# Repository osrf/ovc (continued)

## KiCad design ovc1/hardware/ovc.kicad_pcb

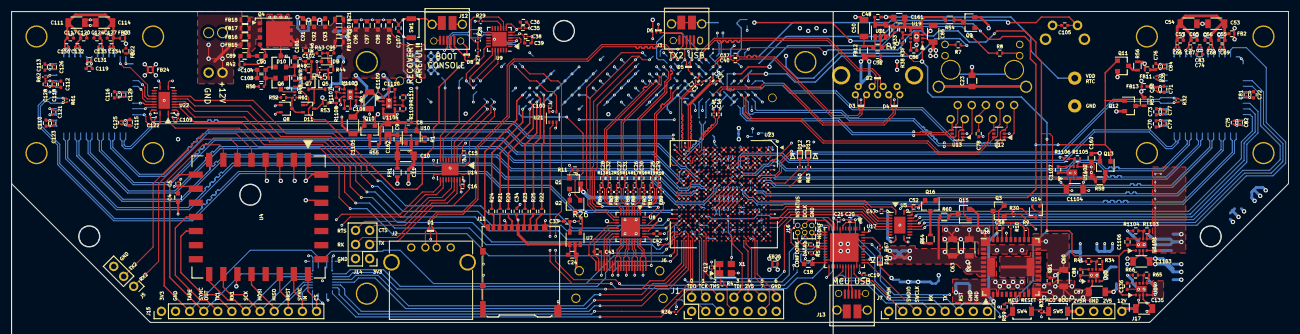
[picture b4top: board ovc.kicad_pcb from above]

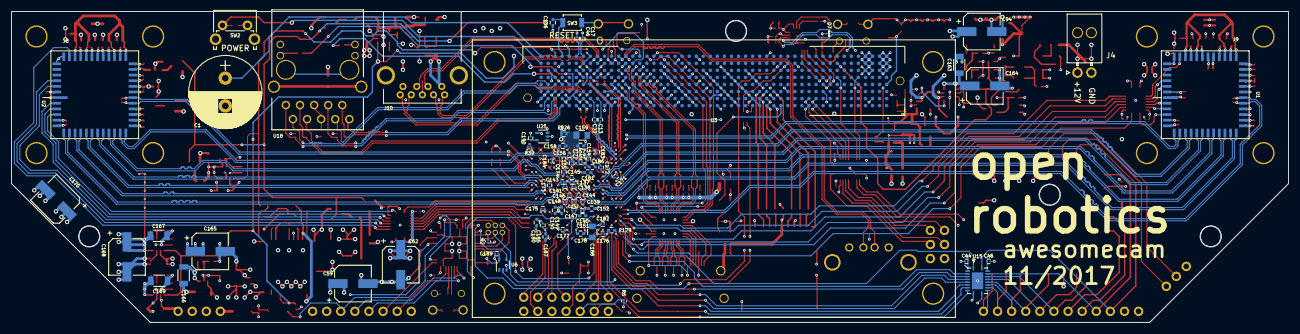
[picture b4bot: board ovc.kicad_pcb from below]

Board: 6 copper layers, 230.0 x 56.0 mm, 379 parts (80 on the bottom side), 315 nets.

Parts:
C1: 100m; CP_Radial_D13.0mm_P5.00mm
C2, C3, C5, C6, C7, C13, C14, C15, C16, C17, C19, C20, C21, C22, C25, C26, C27, C28, C29, C30, C31, C32, C35, C37, C38, C40, C41, C44, C45, C46, C47, C52, C77, C79, C80, C81, C82, C83, C84, C100, C109, C121, C122, C123, C125, C126, C128, C129, C131, C146, C147, C154, C155, C175, C176, C183, C184, C189, C190: 100n; C_0201
C4, C9, C18, C24, C49, C91, C92, C93, C96, C97, C98, C99, C103, C104: 10u; C_0603
C8, C11, C34, C42, C48, C51, C61: 100n; C_0402
C10, C50, C53, C54, C63, C64, C111, C114, C163, C166, C167, C169: 100u; C_1206
C12, C75, C118, C143, C171: 10n; C_0201
C23: 100p; C_0805
C33, C43, C102, C150, C158, C179, C187: 1u; C_0402
C36, C39, C55, C56, C57, C65, C74, C76, C116, C117, C119, C120, C124, C127, C151, C152, C180, C181: 4u7; C_0402
C58, C78: 10n; C_0402
C59, C94: 100u; CP_Elec_6.3x7.7
C60, C85, C87, C135, C1103, C1104, C1105, C1109: 47u; C_1206
C62, C164, C165, C168, C170: 220u; CP_Elec_6.3x5.8
C66, C67, C68, C69, C130, C132, C133, C134: 1u; C_0201
C70, C71, C72, C73, C110, C112, C113, C115: 10u; C_0402
C86, C88, C108, C136, C1106, C1107, C1110: 4n7; C_0402
C89: 100n; C_0603
C90: 4u7; C_0603
C95, C149, C157, C178, C186: 470n; C_0402
C101: 2u2; C_0603
C105, C106, C107: 1n; C_0402
C137, C138, C139, C140, C141, C142, C153, C172, C182: 22n; C_0201
C144, C145, C173, C174: 47n; C_0201
C148, C156, C177, C185: 220n; C_0201
C159, C188: 100u; C_0805
C160: 22u; C_0603
C161, C162: 22u; C_0805
D1, D2, D3, D4, D5, D6, D7, D8: TPD2EUSB30A; TPD2EUSB30x
D9: RB521S30T1G; D_SOD-523
D10: BAT54ALT1G; SOT-23
D11: BAT54CW-7-F; SOT-323_SC-70
D12, D14: LED_Red; LED_0402
D13: LED_Green; LED_0402
FB1, FB12: 220; R_0603
FB2, FB11, FB13, FB22, FB23, FB24: 220; R_0402
FB3, FB4, FB5, FB6, FB7, FB8, FB9, FB10: 600; R_0201
FB15, FB16, FB17, FB18, FB19, FB20, FB21: 30; R_0603
FB25, FB26: 60; R_0402
J1: FPGA DEBUG; Pin_Header_Straight_2x07_Pitch2.54mm
J2: USB_A
J3, J12, J13: USB_OTG; USB_Micro-B_10103594-0001LF
J4: POWER; Molex_NanoFit_1x02x2.50mm_Angled
J5: IMU DEBUG; Pin_Header_Straight_1x03_Pitch2.54mm
J6: HDMI_TYPE_A; AMP_FCI_10029449-111RLF_HDMI_TYPE_A
J7: MCU DEBUG; Pin_Header_Straight_1x08_Pitch2.54mm
J8, J9: LENS_HOLDER; M12_PYTHON1300_M3Mounting
J10: USB3_A; wurth_692121030100
J11: Micro_SD_Card_Det_Hirose_DM3AT; Hirose_DM3AT-SF-PEJM5
J14: DEBUG UART; Pin_Header_Straight_2x03_Pitch2.54mm
J15: IMU; Pin_Header_Straight_1x12_Pitch2.54mm
J16: FPGA CONFIG; Pin_Header_Straight_2x03_Pitch1.27mm
J17: POWER DEBUG; Pin_Header_Straight_1x04_Pitch2.54mm
Q1: Q_NMOS_GSD; SOT-23
Q2, Q3: DMN2041L; SOT-23
Q4: AON6407; TDSON-8-1
Q5, Q7, Q8, Q14: NTS4001NT1G; SOT-323_SC-70
Q6: MMBT4403; SOT-23
Q9, Q10, Q11, Q12, Q13, Q15, Q16: NTR4003NT1G; SOT-23
R1, R11, R33, R42, R44, R46, R47, R48: 10k; R_0402
R2, R3, R4, R5, R6, R27, R28, R30, R31: 10k; R_0201
R7, R8: 681; R_0402
R9: 1M; R_0201
R10: 1k74; R_0201
R12, R13, R14, R15, R16, R17, R18, R19: 499; R_0201
R20: 0; R_0402
R21, R22, R23, R24, R25: 10; R_0402
R26, R35, R45, R51, R62: 47k; R_0201
R29, R36: 1k; R_0201
R32, R61: 100; R_0201
R34, R65: 215k; R_0402
R37, R1109: 523k; R_0402
R38, R41, R43, R49, R52, R53, R59, R66, R1104, R1106, R1108, R1110: 100k; R_0402
R39: 2k; R_0201
R40, R63, R67: 330; R_0201
R50: 10M; R_0402
R54, R55: 100; R_0603
R56, R57, R58, R60, R64: 47; R_0603
R1103: 316k; R_0402
R1105: 49k9; R_0402
R1107: 124k; R_0402
SW1: recovery; SW_SPST_B3U-1000P
SW2: SW_Push; SW_Tactile_SPST_Angled_PTS645Vx58-2LFS
SW3: SW_Push; SW_SPST_B3U-1000P
SW4: RESET; SW_SPST_B3U-1000P
SW5: BOOT; SW_SPST_B3U-1000P
U1, U2: NOIP1SN1300A-QDI; LCC101.6P1422X1422X165-48
U3: Jetson; JETSON_TX
U4: VN-100
U5, U14, U15, U22: TXB0108RGY; TI_VQFN_20_RGY
U6, U21, U25: 74LVC1G34; SOT-353_SC-70-5
U7: NCP380LSN10AAT1G; SOT-23-5
U8: IP4786CZ32; QFN-32-1EP_5x5mm_Pitch0.5mm
U9: CP2102N-A01-GQFN24; QFN-24-1EP_4x4mm_Pitch0.5mm
U10, U11: TPS2069C; SOT-23-5
U12, U13: SP3002-04JTG; SOT-363_SC-70-6
U16: LMZ31707; TI_RVQ_42
U17: STM32L452CE; QFN-48-1EP_7x7mm_Pitch0.5mm
U18: ARJ11C-MBSAS-A-BA-7MU2
U19, U20, U24, U1101, U1102, U1103, U1104: TPS82130
U23: 5CGTFD5C5U19I7N; INTEL_U484
X1: ASEMB-100MHz; Oscillator_SMD_Abracon_ASE-4pin_3.2x2.5mm

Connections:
2V5_MCU: C18.1, C19.1, C21.1, C165.1, C166.1, C189.1, J7.1, J17.4, R30.1, R34.1, R59.2, SW5.1, U6.5, U17.1, U17.9, U17.24, U17.36, U17.48, U20.4, U20.5
+1V1: C62.1, C63.1, C64.1, C137.1, C138.1, C139.1, C140.1, C141.1, C142.1, C143.1, C144.1, C145.1, C146.1, C147.1, C148.1, C149.1, C150.1, C151.1, C152.1, R60.1, U16.27, U16.34, U16.35, U16.36, U16.37, U16.38, U16.41, U23.H11, U23.H13, U23.H15, U23.J10, U23.J12, U23.J14, U23.K9, U23.K11, U23.K13, U23.L10, U23.L12, U23.L14, U23.M11, U23.M13, U23.M15, U23.N12, U23.N14, U23.P11, U23.P13, U23.P15
+1V2: C160.1, FB26.2, R58.1, R1105.1, U1102.4, U1102.5
+1V8: C15.1, C38.1, C39.1, C100.1, C163.1, C164.1, FB13.2, FB24.2, R29.2, R57.1, R1107.1, U8.27, U8.28, U9.5, U14.2, U14.10, U17.38, U21.5, U1103.4, U1103.5
+2V5: C12.1, C44.1, C47.1, C109.1, C169.1, C170.1, C171.1, C172.1, C173.1, C174.1, C175.1, C176.1, C177.1, C178.1, C179.1, C180.1, C181.1, C190.1, FB25.2, J1.9, J17.2, R2.1, R3.1, R4.1, R5.1, R6.1, R64.1, R65.1, U5.2, U5.10, U15.2, U15.10, U22.2, U22.10, U23.A6, U23.A16, U23.AA6, U23.AA21, U23.AB9, U23.AB14, U23.B7, U23.B9, U23.B19, U23.C5, U23.C12, U23.D15, U23.E8, U23.E9, U23.E15, U23.E18, U23.F9, U23.F13, U23.G19, U23.H7, U23.H17, U23.H22, U23.K18, U23.L21, U23.M18, U23.N17, U23.N19, U23.P17, U23.P20, U23.R8, U23.R18, U23.T6, U23.T16, U23.T21, U23.U20, U23.V6, U23.V7, U23.V10, U23.V12, U23.V14, U23.V16, U23.W9, U23.W10, U23.W15, U23.Y6, U23.Y18, U24.4, U24.5, U25.5, X1.1, X1.4
+3V3: C4.1, C5.1, C16.1, C33.1, C35.1, C36.1, C45.1, C52.1, C122.1, C167.1, C168.1, FB2.2, FB11.2, FB22.2, FB23.2, J14.1, J15.1, R11.1, R26.1, R56.1, R1103.1, U4.10, U5.19, U7.5, U9.6, U9.7, U14.19, U15.19, U18.12, U18.13, U22.19, U1101.4, U1101.5
+5V: C8.1, C162.1, R55.1, R1109.1, U8.11, U10.5, U1104.4, U1104.5
+12V: C59.1, C60.1, C61.1, C85.1, C87.1, C91.1, C92.1, C93.1, C95.1, C135.1, C1103.1, C1104.1, C1105.1, C1109.1, D10.3, FB19.2, FB20.2, FB21.2, J17.1, Q4.5, R46.1, R51.1, U16.1, U16.3, U16.11, U16.12, U16.39, U16.40, U19.2, U20.2, U24.2, U1101.2, U1102.2, U1103.2, U1104.2
/IMU/CS_3V3: J15.12, U4.23, U15.12
/IMU/MISO_3V3: J15.9, U4.19, U15.15
/IMU/MOSI_3V3: J15.8, U4.17, U15.16
/IMU/NRST_3V3: J15.10, U4.21, U15.14
/IMU/RX2: J5.1, U4.6
/IMU/SCK_3V3: J15.7, U4.16, U15.17
/IMU/SYNC_IN_3V3: J15.11, U4.22, U15.13
/IMU/SYNC_OUT_3V3: J15.4, U4.9, U15.18
/IMU/TARE_3V3: J15.3, U4.7, U15.20
/IMU/TX2: J5.2, U4.5
/fpga_bank_5b/CLK100: U23.L17, X1.3
/fpga_bank_8a/LED0: R40.2, U23.A9
/fpga_bank_8a/LED1: R63.2, U23.A10
/fpga_config/TCK: J1.3, R36.1, U23.V5
/fpga_config/TDI: J1.7, R4.2, U23.P5
/fpga_config/TDO: J1.1, U23.V3
/fpga_config/TMS: J1.5, R6.2, U23.R4
/fpga_pcie/GXB_TX_L0+: C22.2, U23.Y4
/fpga_pcie/GXB_TX_L0-: C13.2, U23.Y3
/fpga_pcie/GXB_TX_L1+: C14.2, U23.U2
/fpga_pcie/GXB_TX_L1-: C41.2, U23.U1
/fpga_pcie/REFCLK+: C17.2, U23.V4
/fpga_pcie/REFCLK-: C46.2, U23.U4
/fpga_power/RREF_TL: R39.1, U23.A1
/fpga_power/VCC_AUX: C182.1, C183.1, C184.1, C185.1, C186.1, C187.1, C188.1, FB25.1, U23.A3, U23.AA12, U23.AB5, U23.D6, U23.D12, U23.D19, U23.E19, U23.F4, U23.M3, U23.T3, U23.T4, U23.U18, U23.W19
/fpga_power/VCC_GXBL: C153.1, C154.1, C155.1, C156.1, C157.1, C158.1, C159.1, FB26.1, U23.J4, U23.K3, U23.K5, U23.L4, U23.N4, U23.P3
/imagers/CAM1_1V8: C112.1, C115.1, C118.1, C121.1, C125.1, C128.1, FB24.1, U1.6, U1.22, U1.26
/imagers/CAM1_3V3: C110.1, C113.1, C116.1, C119.1, C123.1, C126.1, C129.1, C131.1, FB22.1, U1.1, U1.19, U1.29, U1.36
/imagers/CAM1_CS_3V3: U1.47, U22.16
/imagers/CAM1_MISO_3V3: U1.3, U22.18
/imagers/CAM1_MOSI_3V3: U1.2, U22.17
/imagers/CAM1_RST_3V3: U1.46, U22.15
/imagers/CAM1_SCK_3V3: U1.4, U22.20
/imagers/CAM1_TRG_3V3: U1.41, U22.14
/imagers/CAM1_VDDPIX: C111.1, C114.1, C117.1, C120.1, C124.1, C127.1, C130.1, C132.1, C133.1, C134.1, FB23.1, U1.31, U1.33, U1.38, U1.40
/imagers/CAM2_1V8: C71.1, C73.1, C75.1, C77.1, C80.1, C82.1, FB13.1, U2.6, U2.22, U2.26
/imagers/CAM2_3V3: C70.1, C72.1, C74.1, C76.1, C79.1, C81.1, C83.1, C84.1, FB11.1, U2.1, U2.19, U2.29, U2.36
/imagers/CAM2_CS_3V3: U2.47, U5.16
/imagers/CAM2_MISO_3V3: U2.3, U5.18
/imagers/CAM2_MOSI_3V3: U2.2, U5.17
/imagers/CAM2_RST_3V3: U2.46, U5.15
/imagers/CAM2_SCK_3V3: U2.4, U5.20
/imagers/CAM2_TRG_3V3: U2.41, U5.14
/imagers/CAM2_VDDPIX: C53.1, C54.1, C55.1, C56.1, C57.1, C65.1, C66.1, C67.1, C68.1, C69.1, FB2.1, U2.31, U2.33, U2.38, U2.40
/jetson_enet/GBE_MDI0+: U3.E48, U12.1, U18.1
/jetson_enet/GBE_MDI0-: U3.E49, U12.3, U18.2
/jetson_enet/GBE_MDI1+: U3.F47, U12.6, U18.3
/jetson_enet/GBE_MDI1-: U3.F48, U12.4, U18.4
/jetson_enet/GBE_MDI2+: U3.G48, U13.1, U18.7
/jetson_enet/GBE_MDI2-: U3.G49, U13.3, U18.8
/jetson_enet/GBE_MDI3+: U3.H47, U13.6, U18.9
/jetson_enet/GBE_MDI3-: U3.H48, U13.4, U18.10
/jetson_enet/LINK_1G: R8.1, U18.11
/jetson_enet/LINK_ACT: R7.1, U18.14
/jetson_hdmi/CEC: U3.B33, U8.29
/jetson_hdmi/CEC_CON: J6.13, U8.25
/jetson_hdmi/DDC_CLK: U3.A35, U8.9
/jetson_hdmi/DDC_CLK_CON: J6.15, U8.15
/jetson_hdmi/DDC_DAT: U3.A34, U8.10
/jetson_hdmi/DDC_DAT_CON: J6.16, U8.14
/jetson_hdmi/ESD_BYP: C42.1, U8.26
/jetson_hdmi/HDMI_TXC+: C32.2, U3.E36
/jetson_hdmi/HDMI_TXC-: C28.2, U3.E35
/jetson_hdmi/HDMI_TXD0+: C31.2, U3.D37
/jetson_hdmi/HDMI_TXD0-: C27.2, U3.D36
/jetson_hdmi/HDMI_TXD1+: C30.2, U3.C38
/jetson_hdmi/HDMI_TXD1-: C26.2, U3.C37
/jetson_hdmi/HDMI_TXD2+: C29.2, U3.E39
/jetson_hdmi/HDMI_TXD2-: C25.2, U3.E38
/jetson_hdmi/HPD: U3.A33, U8.32
/jetson_hdmi/HPDET_CON: J6.19, U8.12
/jetson_hdmi/TMDS_CON_CK+: J6.10, U8.18
/jetson_hdmi/TMDS_CON_CK-: J6.12, U8.17
/jetson_hdmi/TMDS_CON_D0+: J6.7, U8.20
/jetson_hdmi/TMDS_CON_D0-: J6.9, U8.19
/jetson_hdmi/TMDS_CON_D1+: J6.4, U8.22
/jetson_hdmi/TMDS_CON_D1-: J6.6, U8.21
/jetson_hdmi/TMDS_CON_D2+: J6.1, U8.24
/jetson_hdmi/TMDS_CON_D2-: J6.3, U8.23
/jetson_hdmi/TMDS_SYS_CK+: C32.1, R12.1, U8.7
/jetson_hdmi/TMDS_SYS_CK-: C28.1, R13.1, U8.8
/jetson_hdmi/TMDS_SYS_D0+: C31.1, R14.1, U8.5
/jetson_hdmi/TMDS_SYS_D0-: C27.1, R15.1, U8.6
/jetson_hdmi/TMDS_SYS_D1+: C30.1, R16.1, U8.3
/jetson_hdmi/TMDS_SYS_D1-: C26.1, R17.1, U8.4
/jetson_hdmi/TMDS_SYS_D2+: C29.1, R18.1, U8.1
/jetson_hdmi/TMDS_SYS_D2-: C25.1, R19.1, U8.2
/jetson_hdmi/UTILTY_CON: J6.14, U8.16
/jetson_pcie/PEX0_TX+: C6.2, U3.E44
/jetson_pcie/PEX0_TX-: C2.2, U3.E45
/jetson_pcie/PEX1_TX+: C7.2, U3.D42
/jetson_pcie/PEX1_TX-: C3.2, U3.D43
/jetson_power/POWER_BTN: C105.1, SW2.1, U3.B50
/jetson_power/RESET_IN: C106.1, SW3.1, U3.A47
/jetson_power/VDD_RTC: C1.1, U3.A50
/jetson_sdcard/SDCARD_CD: J11.9, U3.F17
/jetson_sdcard/SDCARD_CLK: J11.5, R20.1
/jetson_sdcard/SDCARD_CMD: J11.3, R23.1
/jetson_sdcard/SDCARD_D0: J11.7, R21.1
/jetson_sdcard/SDCARD_D1: J11.8, R24.1
/jetson_sdcard/SDCARD_D2: J11.1, R22.1
/jetson_sdcard/SDCARD_D3: J11.2, R25.1
/jetson_sdcard/SDCARD_PWR_EN: Q2.1, U3.H16
/jetson_sdcard/SDCARD_VDD: C24.1, C34.1, J11.4, U7.1
/jetson_uarts/UART0_CTS: U3.H11, U14.4
/jetson_uarts/UART0_CTS_3V3: J14.5, U14.17
/jetson_uarts/UART0_RTS: U3.G11, U14.5
/jetson_uarts/UART0_RTS_3V3: J14.6, U14.16
/jetson_uarts/UART0_RX: U3.G12, U14.3
/jetson_uarts/UART0_RX_3V3: J14.4, U14.18
/jetson_uarts/UART0_TX: U3.H12, U14.1
/jetson_uarts/UART0_TX_3V3: J14.3, U14.20
/jetson_uarts/UART1_CTS: U3.E10, U9.19
/jetson_uarts/UART1_RTS: U3.E9, U9.18
/jetson_uarts/UART1_RX: U3.D10, U9.21
/jetson_uarts/UART1_TX: U3.D9, U9.20
/jetson_uarts/UART7_RX: U3.D5, U14.9
/jetson_uarts/UART7_TX: U3.D8, U14.8
/jetson_uarts/USBD+: D7.2, J12.3, U9.3
/jetson_uarts/USBD-: D7.1, J12.2, U9.4
/jetson_uarts/VBUS_DIV: R27.2, R28.1, U9.8
/jetson_usb/SS1_TX+: C37.2, U3.C43
/jetson_usb/SS1_TX-: C40.2, U3.C44
/jetson_usb/USB1_D+: D1.1, J2.3, U3.A38
/jetson_usb/USB1_D-: D1.2, J2.2, U3.A39
/jetson_usb/USB1_EN: R1.1, U3.A18, U10.4
/jetson_usb/USB1_VBUS: C11.1, FB1.2, J2.1
/mcu/BOOT0: R31.1, SW5.2, U17.44
/mcu/LED: R67.2, U17.46
/mcu/NRST: C20.1, J7.6, SW4.1, U17.7
/mcu/STDIN: J7.4, U17.31
/mcu/STDOUT: J7.5, U17.30
/mcu/SWCLK: J7.3, U17.37
/mcu/SWDIO: J7.2, U17.34
/mcu/USART2_RX: U6.4, U17.13
/mcu/USART2_TX: U17.12, U21.2
/mcu/USB_D+: J13.3, U17.33
/mcu/USB_D-: J13.2, U17.32
/power/AGND: C58.2, Q3.2, R9.2, R10.2, U16.2, U16.23, U16.29
/power/DISCHARGE: D11.3, Q9.1, Q10.1, Q11.1, Q12.1, Q13.1, Q15.1, Q16.1, R53.1
/power/DROP_DETECT: C102.1, D11.1, Q7.1, R48.2, R49.1
/power/PG_GRP1: R59.1, U16.8, U19.1, U24.1, U1101.1, U1103.1, U1104.1
/power/PH: U16.10, U16.13, U16.14, U16.15, U16.16, U16.17, U16.18, U16.19, U16.42
/power/VIN: FB15.2, FB16.2, FB17.2, FB18.2, J4.1
/power/~PWR_EN: D11.2, Q8.3, R51.2, R52.1
/power/~PWR_EN_GRP1: Q3.1, Q14.3, R30.2
CAM1_CLKIN+: R61.2, U1.24, U23.AB16
CAM1_CLKIN-: R61.1, U1.23, U23.AB15
CAM1_CLKOUT+: U1.7, U23.P9
CAM1_CLKOUT-: U1.8, U23.R9
CAM1_CS: U22.5, U23.AA18
CAM1_DOUT0+: U1.9, U23.U8
CAM1_DOUT0-: U1.10, U23.V9
CAM1_DOUT1+: U1.11, U23.AA9
CAM1_DOUT1-: U1.12, U23.Y9
CAM1_DOUT2+: U1.13, U23.T10
CAM1_DOUT2-: U1.14, U23.R10
CAM1_DOUT3+: U1.15, U23.U10
CAM1_DOUT3-: U1.16, U23.U11
CAM1_MISO: U22.3, U23.AA17
CAM1_MOSI: U22.4, U23.AB20
CAM1_RST: U22.6, U23.AB18
CAM1_SCK: U22.1, U23.AA20
CAM1_SYNC+: U1.17, U23.N9
CAM1_SYNC-: U1.18, U23.N10
CAM1_TRG: U22.7, U23.AB17
CAM2_CLKIN+: R32.2, U2.24, U23.A7
CAM2_CLKIN-: R32.1, U2.23, U23.A8
CAM2_CLKOUT+: U2.7, U23.G10
CAM2_CLKOUT-: U2.8, U23.F10
CAM2_CS: U5.5, U23.A17
CAM2_DOUT0+: U2.9, U23.D11
CAM2_DOUT0-: U2.10, U23.E11
CAM2_DOUT1+: U2.11, U23.C10
CAM2_DOUT1-: U2.12, U23.C9
CAM2_DOUT2+: U2.13, U23.D9
CAM2_DOUT2-: U2.14, U23.D8
CAM2_DOUT3+: U2.15, U23.H8
CAM2_DOUT3-: U2.16, U23.G7
CAM2_MISO: U5.3, U23.A14
CAM2_MOSI: U5.4, U23.A15
CAM2_RST: U5.6, U23.A18
CAM2_SCK: U5.1, U23.A13
CAM2_SYNC+: U2.17, U23.G6
CAM2_SYNC-: U2.18, U23.H6
CAM2_TRG: U5.7, U23.A19
FPGA_AUX0: J1.2, U23.U22
FPGA_AUX1: J1.4, U23.U21
FPGA_AUX2: J1.6, U23.T22
FPGA_AUX3: J1.8, U23.J21
FPGA_AUX4: J1.10, U23.G22
FPGA_AUX5: J1.12, U23.G21
FPGA_AUX6: J1.14, U23.D22
FPGA_AUX7: J1.11, U23.E21
FPGA_CONFIG_DATA0: J16.3, U17.17, U23.AB4
FPGA_CONFIG_DCLK: J16.4, U17.11, U23.M5
FPGA_CONF_DONE: J16.1, R3.2, U17.18, U23.J6
FPGA_CVP_CONF_DONE: U17.10, U23.T20
FPGA_NCONFIG: J16.5, R2.2, U17.14, U23.A4
FPGA_NSTATUS: J16.2, R5.2, U17.19, U23.G5
GND: C1.2, C4.2, C5.2, C8.2, C9.2, C10.2, C11.2, C12.2, C15.2, C16.2, C18.2, C19.2, C20.2, C21.2, C23.2, C24.2, C33.2, C34.2, C35.2, C36.2, C38.2, C39.2, C42.2, C43.2, C44.2, C45.2, C47.2, C48.2, C49.2, C50.2, C51.2, C52.2, C53.2, C54.2, C55.2, C56.2, C57.2, C59.2, C60.2, C61.2, C62.2, C63.2, C64.2, C65.2, C66.2, C67.2, C68.2, C69.2, C70.2, C71.2, C72.2, C73.2, C74.2, C75.2, C76.2, C77.2, C78.1, C79.2, C80.2, C81.2, C82.2, C83.2, C84.2, C85.2, C86.2, C87.2, C88.2, C89.2, C91.2, C92.2, C93.2, C94.2, C96.2, C97.2, C98.2, C99.2, C100.2, C101.2, C102.2, C103.2, C104.2, C105.2, C106.2, C107.2, C108.2, C109.2, C110.2, C111.2, C112.2, C113.2, C114.2, C115.2, C116.2, C117.2, C118.2, C119.2, C120.2, C121.2, C122.2, C123.2, C124.2, C125.2, C126.2, C127.2, C128.2, C129.2, C130.2, C131.2, C132.2, C133.2, C134.2, C135.2, C136.2, C137.2, C138.2, C139.2, C140.2, C141.2, C142.2, C143.2, C144.2, C145.2, C146.2, C147.2, C148.2, C149.2, C150.2, C151.2, C152.2, C153.2, C154.2, C155.2, C156.2, C157.2, C158.2, C159.2, C160.2, C161.2, C162.2, C163.2, C164.2, C165.2, C166.2, C167.2, C168.2, C169.2, C170.2, C171.2, C172.2, C173.2, C174.2, C175.2, C176.2, C177.2, C178.2, C179.2, C180.2, C181.2, C182.2, C183.2, C184.2, C185.2, C186.2, C187.2, C188.2, C189.2, C190.2, C1103.2, C1104.2, C1105.2, C1106.2, C1107.2, C1109.2, C1110.2, D1.3, D2.3, D3.3, D4.3, D5.3, D6.3, D7.3, D8.3, D9.2, D12.1, D13.1, D14.1, J1.13, J2.4, J2.5, J3.5, J3.6, J4.2, J5.3, J6.2, J6.5, J6.8, J6.11, J6.17, J6.20, J7.7, J7.8, J10.4, J10.7, J11.6, J11.10, J11.11, J12.5, J12.6, J13.5, J13.6, J14.2, J15.2, J16.6, J17.3, Q1.2, Q2.2, Q5.2, Q7.2, Q8.2, Q9.2, Q10.2, Q11.2, Q12.2, Q13.2, Q14.2, Q15.2, Q16.2, R28.2, R31.2, R35.2, R36.2, R38.2, R39.2, R41.2, R42.2, R43.2, R45.2, R46.2, R47.2, R49.2, R50.2, R52.2, R53.2, R62.2, R66.2, R1104.2, R1106.2, R1108.2, R1110.2, SW1.2, SW2.2, SW3.2, SW4.2, U1.5, U1.20, U1.21, U1.25, U1.27, U1.30, U1.32, U1.34, U1.35, U1.37, U1.39, U1.42, U1.43, U1.48, U2.5, U2.20, U2.21, U2.25, U2.27, U2.30, U2.32, U2.34, U2.35, U2.37, U2.39, U2.42, U2.43, U2.48, U3.A3, U3.A4, U3.A28, U3.A37, U3.A40, U3.A43, U3.B3, U3.B4, U3.B14, U3.B31, U3.B38, U3.B41, U3.B44, U3.B47, U3.C3, U3.C4, U3.C21, U3.C24, U3.C27, U3.C30, U3.C33, U3.C36, U3.C39, U3.C42, U3.C45, U3.D20, U3.D23, U3.D26, U3.D29, U3.D32, U3.D35, U3.D38, U3.D41, U3.D44, U3.E19, U3.E22, U3.E25, U3.E28, U3.E31, U3.E34, U3.E37, U3.E40, U3.E43, U3.E46, U3.F10, U3.F15, U3.F21, U3.F24, U3.F27, U3.F30, U3.F33, U3.F36, U3.F39, U3.F40, U3.F41, U3.F42, U3.F45, U3.F49, U3.G3, U3.G17, U3.G20, U3.G23, U3.G26, U3.G29, U3.G32, U3.G35, U3.G38, U3.G39, U3.G40, U3.G41, U3.G44, U3.G45, U3.G46, U3.G47, U3.G50, U3.H19, U3.H22, U3.H25, U3.H28, U3.H31, U3.H34, U3.H37, U3.H40, U3.H41, U3.H42, U3.H43, U3.H46, U3.H49, U4.1, U4.2, U4.3, U4.4, U4.18, U4.28, U4.30, U5.11, U5.21, U6.3, U7.2, U8.33, U9.2, U9.25, U10.2, U11.2, U12.2, U13.2, U14.11, U14.21, U15.11, U15.21, U16.20, U16.21, U16.31, U16.32, U16.33, U17.8, U17.23, U17.35, U17.47, U17.49, U19.3, U19.9, U20.3, U20.9, U21.3, U22.11, U22.21, U23.A2, U23.A5, U23.A11, U23.A21, U23.AA3, U23.AA4, U23.AA11, U23.AA14, U23.AA16, U23.AB1, U23.AB2, U23.AB12, U23.AB19, U23.B1, U23.B2, U23.B10, U23.B14, U23.C1, U23.C2, U23.C3, U23.C4, U23.C7, U23.C17, U23.C22, U23.D1, U23.D2, U23.D5, U23.D10, U23.D16, U23.D20, U23.E3, U23.E4, U23.E5, U23.E13, U23.F1, U23.F2, U23.F3, U23.F5, U23.F6, U23.F11, U23.F16, U23.F21, U23.G1, U23.G2, U23.G3, U23.G4, U23.G9, U23.H1, U23.H2, U23.H3, U23.H4, U23.H5, U23.H14, U23.J3, U23.J5, U23.J11, U23.J13, U23.J15, U23.J20, U23.K1, U23.K2, U23.K4, U23.K6, U23.K8, U23.K10, U23.K12, U23.K14, U23.K20, U23.L1, U23.L2, U23.L3, U23.L5, U23.L6, U23.L11, U23.L13, U23.L16, U23.M1, U23.M2, U23.M4, U23.M9, U23.M12, U23.M14, U23.M19, U23.N3, U23.N5, U23.N7, U23.N11, U23.N13, U23.N15, U23.N22, U23.P1, U23.P2, U23.P4, U23.P10, U23.R1, U23.R2, U23.R3, U23.R13, U23.T1, U23.T2, U23.T11, U23.U3, U23.U5, U23.U9, U23.U14, U23.U19, U23.V1, U23.V2, U23.V17, U23.V21, U23.V22, U23.W3, U23.W4, U23.W6, U23.W20, U23.Y1, U23.Y2, U23.Y5, U23.Y8, U23.Y13, U24.3, U24.9, U25.3, U1101.3, U1101.9, U1102.3, U1102.9, U1103.3, U1103.9, U1104.3, U1104.9, X1.2
HDMI_PULLDOWNS: Q1.1, R11.2
IMU_CS: U15.9, U23.W21
IMU_MISO: U15.6, U23.Y22
IMU_MOSI: U15.5, U23.Y21
IMU_NRST: U15.1, U23.AB21
IMU_RX1: J15.6, U4.13, U14.13
IMU_SCK: U15.4, U23.AA22
IMU_SYNC_IN: U15.8, U23.W22
IMU_SYNC_OUT: U15.3, U23.AB22
IMU_TARE: U15.7, U23.Y20
IMU_TX1: J15.5, U4.12, U14.12
JETSON_CARRIER_PWR_ON: Q8.1, Q14.1, U3.A48, U1102.1
JETSON_PWR_BAD: Q5.3, Q7.3, U3.B8
JETSON_RESET_OUT: U3.A46, U1103.7
JETSON_VDD_MOD: C94.1, C96.1, C97.1, C98.1, C99.1, FB19.1, FB20.1, FB21.1, U3.A1, U3.A2, U3.B1, U3.B2, U3.C1, U3.C2
MCU_RX: U3.B16, U6.2
MCU_TX: U3.B15, U21.4
unnamed: C9.1, C10.1, FB1.1, U10.1
unnamed: C23.1, U18.SHLD
unnamed: C43.1, J6.18, U8.13
unnamed: C49.1, C50.1, FB12.1, U11.1
unnamed: C58.1, U16.28
unnamed: C78.2, U18.5, U18.6
unnamed: C86.1, U19.8
unnamed: C88.1, U20.8
unnamed: C89.1, C90.1, FB15.1, FB16.1, FB17.1, FB18.1, Q4.1, Q4.2, Q4.3
unnamed: C90.2, Q4.4, R42.1
unnamed: C95.2, D9.1, R43.1, R44.1
unnamed: C101.1, D10.2, Q6.1, R47.1
unnamed: C103.1, C104.1, D10.1, Q6.2, R50.1
unnamed: C107.1, SW1.1, U3.E1
unnamed: C108.1, U1103.8
unnamed: C136.1, U24.8
unnamed: C1106.1, U1101.8
unnamed: C1107.1, U1102.8
unnamed: C1110.1, U1104.8
unnamed: D8.1, J12.1, R27.1
unnamed: D12.2, R40.1
unnamed: D13.2, R63.1
unnamed: D14.2, R67.1
unnamed: FB3.1, R12.2
unnamed: FB4.1, R13.2
unnamed: FB5.1, R14.2
unnamed: FB6.1, R15.2
unnamed: FB7.1, R16.2
unnamed: FB8.1, R17.2
unnamed: FB9.1, R18.2
unnamed: FB10.1, R19.2
unnamed: FB3.2, FB4.2, FB5.2, FB6.2, FB7.2, FB8.2, FB9.2, FB10.2, Q1.3
unnamed: Q2.3, R26.2, U7.4
unnamed: Q3.3, U16.30
unnamed: Q5.1, R44.2, R45.1
unnamed: Q6.3, R48.1
unnamed: Q9.3, R54.2
unnamed: Q10.3, R55.2
unnamed: Q11.3, R56.2
unnamed: Q12.3, R57.2
unnamed: Q13.3, R58.2
unnamed: Q15.3, R60.2
unnamed: Q16.3, R64.2
unnamed: R1.2, U10.3
unnamed: R7.2, U3.E47
unnamed: R8.2, U3.F46
unnamed: R9.1, U16.22
unnamed: R10.1, U16.26
unnamed: R20.2, U3.G18
unnamed: R21.2, U3.H18
unnamed: R22.2, U3.F19
unnamed: R23.2, U3.G19
unnamed: R24.2, U3.H17
unnamed: R25.2, U3.F18
unnamed: R29.1, U9.9
unnamed: R33.2, U11.3
unnamed: R34.2, R41.1, U20.6
unnamed: R35.1, U2.28
unnamed: R37.2, R38.1, U19.6
unnamed: R62.1, U1.28
unnamed: R65.2, R66.1, U24.6
unnamed: R1103.2, R1104.1, U1101.6
unnamed: R1105.2, R1106.1, U1102.6
unnamed: R1107.2, R1108.1, U1103.6
unnamed: R1109.2, R1110.1, U1104.6
PCIE_LANE0_RX+: C41.1, U3.H44
PCIE_LANE0_RX-: C14.1, U3.H45
PCIE_LANE0_TX+: C6.1, U23.W2
PCIE_LANE0_TX-: C2.1, U23.W1
PCIE_LANE1_RX+: C13.1, U3.G42
PCIE_LANE1_RX-: C22.1, U3.G43
PCIE_LANE1_TX+: C3.1, U23.AA1
PCIE_LANE1_TX-: C7.1, U23.AA2
PCIE_REFCLK+: C17.1, U3.A44
PCIE_REFCLK-: C46.1, U3.A45
PCIE_RST_2V5: U17.25, U23.R17, U25.4
PCIE_RST_3V3: U3.C49, U25.2
USB0_D+: D5.2, J3.3, U3.B39
USB0_D-: D5.1, J3.2, U3.B40
USB0_ID: D6.2, J3.4, U3.A36
USB0_VBUS: J3.1, U3.B37
USB1_SSRX+: D4.1, J10.6, U3.F43
USB1_SSRX-: D4.2, J10.5, U3.F44
USB1_SSTX+: C37.1, D3.1, J10.9
USB1_SSTX-: C40.1, D3.2, J10.8
USB2_5V: C48.1, C161.1, R33.1, R37.1, R54.1, U11.4, U11.5, U19.4, U19.5
USB2_5V_LIM: C51.1, FB12.2, J10.1
USB2_D+: D2.1, J10.3, U3.B42
USB2_D-: D2.2, J10.2, U3.B43

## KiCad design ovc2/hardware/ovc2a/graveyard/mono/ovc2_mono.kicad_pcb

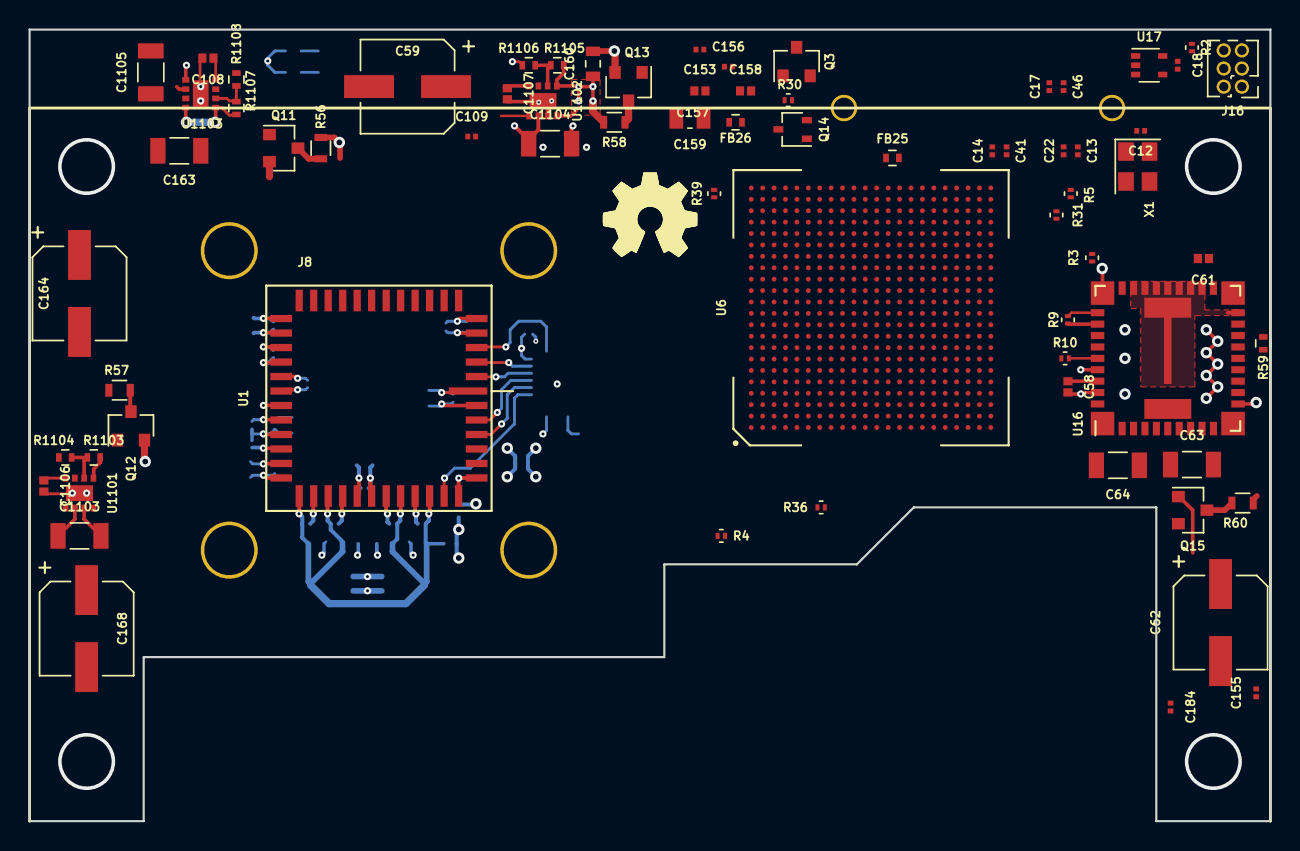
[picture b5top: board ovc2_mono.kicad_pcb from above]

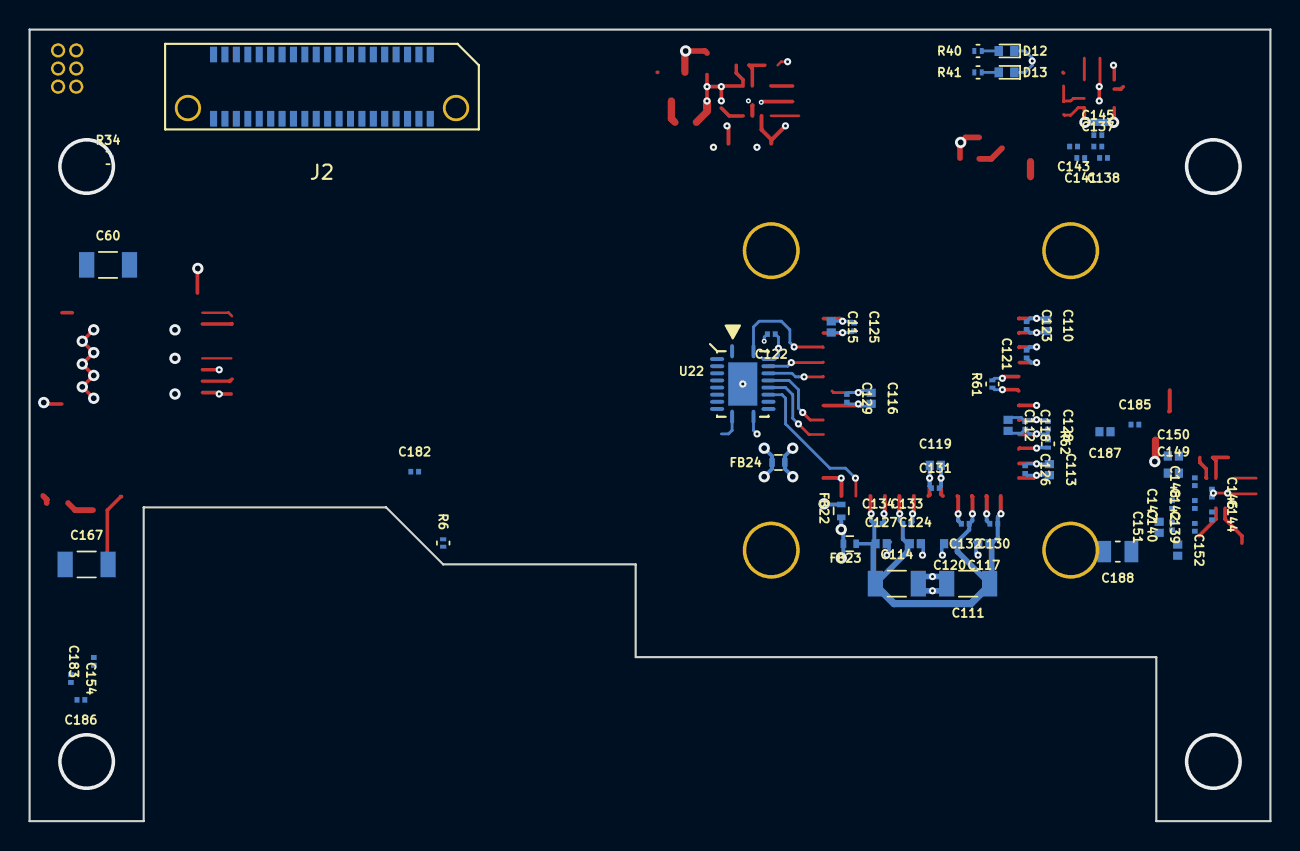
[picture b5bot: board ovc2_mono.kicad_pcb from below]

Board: 6 copper layers, 87.0 x 55.5 mm, 136 parts (63 on the bottom side), 74 nets.

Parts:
C12, C13, C14, C17, C22, C41, C46, C109, C121, C122, C123, C125, C126, C128, C129, C131, C146, C147, C154, C155, C183, C184: 100n; C_0201_0603Metric
C18, C118, C143: 10n; C_0201_0603Metric
C58: 10n; C_0402_1005Metric
C59: 100u; CP_Elec_6.3x7.7
C60, C1103, C1104, C1105: 47u; C_1206_3216Metric
C61: 100n; C_0402_1005Metric
C62, C164, C168: 220u; CP_Elec_6.3x5.8
C63, C64, C111, C114, C163, C167: 100u; C_1206_3216Metric
C108, C1106, C1107: 4n7; C_0402_1005Metric
C110, C112, C113, C115: 10u; C_0402_1005Metric
C116, C117, C119, C120, C124, C127, C151, C152: 4u7; C_0402_1005Metric
C130, C132, C133, C134: 1u; C_0201_0603Metric
C137, C138, C139, C140, C141, C142, C153, C182: 22n; C_0201_0603Metric
C144, C145: 47n; C_0201_0603Metric
C148, C156, C185: 220n; C_0201_0603Metric
C149, C157: 470n; C_0402_1005Metric
C150, C158, C187: 1u; C_0402_1005Metric
C159, C188: 100u; C_0805_2012Metric
C160: 22u; C_0603_1608Metric
C186: 470n; C_0201_0603Metric
D12: LED_Red; LED_0402
D13: LED_Green; LED_0402
FB22, FB23, FB24: 220; R_0402
FB25, FB26: 60; R_0402
J2: Conn_02x20_Odd_Even; SAMTEC_ERF8-020
J8: LENS_HOLDER; M12_PYTHON1300_M3Mounting
J16: FPGA CONFIG; Pin_Header_Straight_2x03_Pitch1.27mm
Q3: DMN2041L; SOT-23
Q11, Q12, Q13, Q15: NTR4003NT1G; SOT-23
Q14: NTS4001NT1G; SOT-323_SC-70
R2, R3, R4, R5, R6, R30: 10k; R_0201
R9: 1M; R_0201
R10: 2k87; R_0201
R31, R39: 2k; R_0201
R34, R36: 1k; R_0201
R40, R41: 330; R_0201
R56, R57, R58, R60: 47; R_0603
R59, R1104, R1106, R1108: 100k; R_0402
R61: 100; R_0201
R62: 47k; R_0201
R1103: 316k; R_0402
R1105: 28k7; R_0402
R1107: 124k; R_0402
U1: NOIP1SN1300A-QDI; LCC101.6P1422X1422X165-48
U6: 10CX220; INTEL_U484
U16: LMZ31707; TI_RVQ_42
U17: 74LVC1G34; SOT-353_SC-70-5
U22: TXB0108RGY; TI_VQFN_20_RGY
U1101, U1102, U1103: TPS82130
X1: ASEMB-100MHz; Oscillator_SMD_Abracon_ASE-4pin_3.2x2.5mm
Z1, Z2: Logo_Open_Hardware_Small; OSHW-Symbol_6.7x6mm_SilkScreen

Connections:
0V9: C62.1, C63.1, C64.1, C137.1, C138.1, C139.1, C140.1, C141.1, C142.1, C143.1, C144.1, C145.1, C146.1, C147.1, C148.1, C149.1, C150.1, C151.1, C152.1, R60.1, U6.J12, U6.J13, U6.K6, U6.K12, U6.K14, U6.K15, U6.K16, U6.L6, U6.L7, U6.L8, U6.L9, U6.L11, U6.L12, U6.L13, U6.L14, U6.L16, U6.M6, U6.M10, U6.M14, U6.M15, U6.M16, U6.N6, U6.N7, U6.N8, U6.N10, U6.N11, U6.N12, U6.N13, U6.N15, U6.N16, U6.P7, U6.P8, U6.P9, U6.P10, U6.P12, U6.P13, U6.P14, U6.P15, U6.R6, U6.R7, U6.R11, U6.R12, U6.R15, U6.R16, U16.27, U16.34, U16.35, U16.36, U16.37, U16.38, U16.41
1V03: C160.1, FB26.2, R58.1, R1105.1, U1102.4, U1102.5
2V5_MCU: R30.1, R59.2
+1V8: C12.1, C18.1, C109.1, C163.1, C164.1, FB24.2, FB25.2, R2.1, R3.1, R4.1, R5.1, R6.1, R34.1, R57.1, R1107.1, U6.C9, U6.D11, U6.D16, U6.F10, U6.F15, U6.H14, U6.J1, U6.J8, U6.J14, U6.K2, U6.K3, U6.R9, U6.R14, U6.T8, U6.T9, U6.T15, U6.U9, U6.U12, U6.V9, U6.V14, U6.W6, U6.Y8, U17.5, U22.2, U22.10, U1103.4, U1103.5, X1.1, X1.4
+3V3: C122.1, C167.1, C168.1, FB22.2, FB23.2, R56.1, R1103.1, U22.19, U1101.4, U1101.5
+12V: C59.1, C60.1, C61.1, C1103.1, C1104.1, C1105.1, U16.1, U16.3, U16.11, U16.12, U16.39, U16.40, U1101.2, U1102.2, U1103.2
/fpga_config/TCK: R36.1, U6.P5
/fpga_config/TDI: R4.2, U6.M4
/fpga_config/TMS: R6.2, U6.L3
/fpga_io/CLK100: U6.AA6, X1.3
/fpga_io/PCIE_RST_1V8: U6.AB8, U17.4
/fpga_pcie/GXB_TX_L0+: C22.2, U6.AA22
/fpga_pcie/GXB_TX_L0-: C13.2, U6.AA21
/fpga_pcie/GXB_TX_L1+: C14.2, U6.W22
/fpga_pcie/GXB_TX_L1-: C41.2, U6.W21
/fpga_pcie/REFCLK+: C17.2, U6.M20
/fpga_pcie/REFCLK-: C46.2, U6.M19
/fpga_power/RREF_BL: R31.1, U6.AB19
/fpga_power/RREF_TL: R39.1, U6.A22
/fpga_power/VCCA: C182.1, C183.1, C184.1, C185.1, C186.1, C187.1, C188.1, FB25.1, U6.L19, U6.M11, U6.M13
/fpga_power/VCC_GXBL: C153.1, C154.1, C155.1, C156.1, C157.1, C158.1, C159.1, FB26.1, U6.J19, U6.J20, U6.N19, U6.N20
/imagers/CAM1_1V8: C112.1, C115.1, C118.1, C121.1, C125.1, C128.1, FB24.1, U1.6, U1.22, U1.26
/imagers/CAM1_3V3: C110.1, C113.1, C116.1, C119.1, C123.1, C126.1, C129.1, C131.1, FB22.1, U1.1, U1.19, U1.29, U1.36
/imagers/CAM1_CS_3V3: U1.47, U22.16
/imagers/CAM1_MISO_3V3: U1.3, U22.18
/imagers/CAM1_MOSI_3V3: U1.2, U22.17
/imagers/CAM1_RST_3V3: U1.46, U22.15
/imagers/CAM1_SCK_3V3: U1.4, U22.20
/imagers/CAM1_TRG_3V3: U1.41, U22.14
/imagers/CAM1_VDDPIX: C111.1, C114.1, C117.1, C120.1, C124.1, C127.1, C130.1, C132.1, C133.1, C134.1, FB23.1, U1.31, U1.33, U1.38, U1.40
/power/AGND: C58.2, Q3.2, R9.2, R10.2, U16.2, U16.23, U16.29
/power/DISCHARGE: Q11.1, Q12.1, Q13.1, Q15.1
/power/PG_GRP1: R59.1, U16.8, U1101.1, U1103.1
/power/PH: U16.10, U16.13, U16.14, U16.15, U16.16, U16.17, U16.18, U16.19, U16.42
/power/~PWR_EN_GRP1: Q3.1, Q14.3, R30.2
CAM1_CLKIN+: R61.2, U1.24
CAM1_CLKIN-: R61.1, U1.23
FPGA_CONFIG_DATA0: J16.3, U6.V7
FPGA_CONFIG_DCLK: J16.4, U6.T2
FPGA_CONF_DONE: J16.1, R3.2, U6.M1
FPGA_NCONFIG: J16.5, R2.2, U6.U5
FPGA_NSTATUS: J16.2, R5.2, U6.L1
GND: C12.2, C18.2, C59.2, C60.2, C61.2, C62.2, C63.2, C64.2, C108.2, C109.2, C110.2, C111.2, C112.2, C113.2, C114.2, C115.2, C116.2, C117.2, C118.2, C119.2, C120.2, C121.2, C122.2, C123.2, C124.2, C125.2, C126.2, C127.2, C128.2, C129.2, C130.2, C131.2, C132.2, C133.2, C134.2, C137.2, C138.2, C139.2, C140.2, C141.2, C142.2, C143.2, C144.2, C145.2, C146.2, C147.2, C148.2, C149.2, C150.2, C151.2, C152.2, C153.2, C154.2, C155.2, C156.2, C157.2, C158.2, C159.2, C160.2, C163.2, C164.2, C167.2, C168.2, C182.2, C183.2, C184.2, C185.2, C186.2, C187.2, C188.2, C1103.2, C1104.2, C1105.2, C1106.2, C1107.2, D12.1, D13.1, J2.16, J2.22, J2.28, J2.31, J2.34, J2.37, J2.39, J2.40, J16.6, Q11.2, Q12.2, Q13.2, Q14.2, Q15.2, R31.2, R36.2, R39.2, R62.2, R1104.2, R1106.2, R1108.2, U1.5, U1.20, U1.21, U1.25, U1.27, U1.30, U1.32, U1.34, U1.35, U1.37, U1.39, U1.42, U1.43, U1.48, U6.A4, U6.A9, U6.A14, U6.A18, U6.A19, U6.A20, U6.A21, U6.AA5, U6.AA10, U6.AA15, U6.AA18, U6.AA19, U6.AA20, U6.AB2, U6.AB7, U6.AB12, U6.AB20, U6.AB21, U6.AB22, U6.B2, U6.B7, U6.B12, U6.B17, U6.B18, U6.B19, U6.B20, U6.B21, U6.B22, U6.C4, U6.C14, U6.C20, U6.D1, U6.D4, U6.D5, U6.D6, U6.D18, U6.D20, U6.D21, U6.D22, U6.E3, U6.E4, U6.E5, U6.E6, U6.E8, U6.E13, U6.E20, U6.E21, U6.E22, U6.F3, U6.F4, U6.F5, U6.F7, U6.F12, U6.F20, U6.F21, U6.F22, U6.G2, U6.G3, U6.G7, U6.G9, U6.G10, U6.G12, U6.G17, U6.G20, U6.H2, U6.H4, U6.H9, U6.H10, U6.H18, U6.H19, U6.H20, U6.H21, U6.H22, U6.J6, U6.J9, U6.J10, U6.J11, U6.J15, U6.J16, U6.J18, U6.J21, U6.J22, U6.K8, U6.K9, U6.K10, U6.K11, U6.K13, U6.K18, U6.K19, U6.K20, U6.K21, U6.K22, U6.L5, U6.L10, U6.L15, U6.L18, U6.L20, U6.M2, U6.M3, U6.M7, U6.M12, U6.M18, U6.M21, U6.M22, U6.N3, U6.N4, U6.N5, U6.N9, U6.N14, U6.N18, U6.N21, U6.N22, U6.P1, U6.P3, U6.P6, U6.P11, U6.P16, U6.P18, U6.P19, U6.P20, U6.P21, U6.P22, U6.R3, U6.R5, U6.R8, U6.R13, U6.R20, U6.T3, U6.T5, U6.T7, U6.T10, U6.T11, U6.T13, U6.T20, U6.T21, U6.T22, U6.U2, U6.U4, U6.U7, U6.U17, U6.U20, U6.V4, U6.V20, U6.V21, U6.V22, U6.W1, U6.W9, U6.W11, U6.W16, U6.W18, U6.W19, U6.W20, U6.Y3, U6.Y13, U6.Y18, U6.Y21, U6.Y22, U16.20, U16.21, U16.31, U16.32, U16.33, U17.3, U22.11, U22.21, U1101.3, U1101.9, U1102.3, U1102.9, U1103.3, U1103.9, X1.2
JETSON_CARRIER_PWR_ON: J2.25, Q14.1, U1102.1
JETSON_RESET_OUT: J2.27, U1103.7
unnamed: C58.1, U16.28
unnamed: C108.1, U1103.8
unnamed: C1106.1, U1101.8
unnamed: C1107.1, U1102.8
unnamed: D12.2, R40.1
unnamed: D13.2, R41.1
unnamed: Q3.3, U16.30
unnamed: Q11.3, R56.2
unnamed: Q12.3, R57.2
unnamed: Q13.3, R58.2
unnamed: Q15.3, R60.2
unnamed: R9.1, U16.22
unnamed: R10.1, U16.26
unnamed: R34.2, U6.L4
unnamed: R62.1, U1.28
unnamed: R1103.2, R1104.1, U1101.6
unnamed: R1105.2, R1106.1, U1102.6
unnamed: R1107.2, R1108.1, U1103.6
PCIE_LANE0_RX+: J2.30, U6.Y20
PCIE_LANE0_RX-: J2.32, U6.Y19
PCIE_LANE0_TX+: C22.1, J2.36
PCIE_LANE0_TX-: C13.1, J2.38
PCIE_LANE1_RX+: J2.18, U6.U22
PCIE_LANE1_RX-: J2.20, U6.U21
PCIE_LANE1_TX+: C14.1, J2.24
PCIE_LANE1_TX-: C41.1, J2.26
PCIE_REFCLK+: C17.1, J2.33
PCIE_REFCLK-: C46.1, J2.35
PCIE_RST_3V3: J2.29, U17.2

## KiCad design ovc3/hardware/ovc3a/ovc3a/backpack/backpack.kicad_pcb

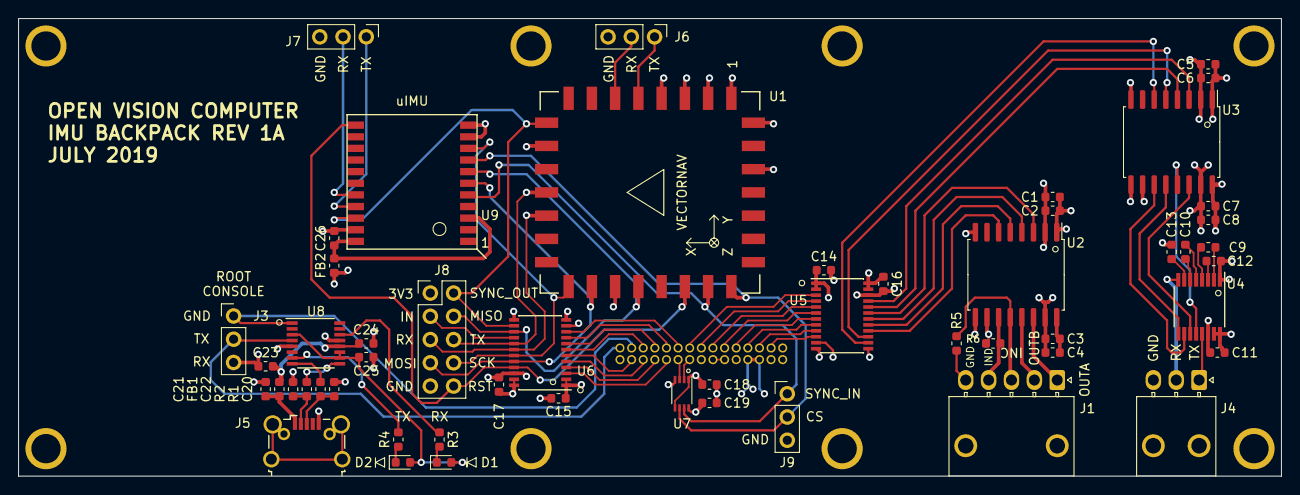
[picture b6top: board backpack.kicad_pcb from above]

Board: 4 copper layers, 138.0 x 50.0 mm, 62 parts (1 on the bottom side), 78 nets.

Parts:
C1, C4, C5, C8, C23: 10u; C_0603_1608Metric
C2, C3, C6, C7, C9, C10, C11, C12, C13, C14, C15, C16, C17, C18, C19, C21, C24, C25, C26: 100n; C_0603_1608Metric
C20, C22: 47p; C_0603_1608Metric
D1: RXLED; LED_0603_1608Metric
D2: TXLED; LED_0603_1608Metric
FB1, FB2: ferrite; R_0603_1608Metric
H1, H2, H3, H4, H5, H6, H7, H8: MountingHole_Pad; MountingHole_3.2mm_M3_DIN965_Pad
J1: GPIO1; Molex_Nano-Fit_105313-xx05_1x05_P2.50mm_Horizontal
J2: TO_CAMERA; PinHeader_2x15_P1.27mm_Vertical
J3: ROOT CONSOLE; PinHeader_1x03_P2.54mm_Vertical
J4: RS232; Molex_Nano-Fit_105313-xx03_1x03_P2.50mm_Horizontal
J5: USB_B_Micro; USB_Micro-B_Wuerth_629105150521_CircularHoles
J6: IMU_UART2; PinHeader_1x03_P2.54mm_Vertical
J7: IMU_UART0; PinHeader_1x03_P2.54mm_Vertical
J8: debug; PinHeader_2x05_P2.54mm_Vertical
J9: debug; PinHeader_1x03_P2.54mm_Vertical
R1, R2: 27R; R_0603_1608Metric
R3, R4: 270R; R_0603_1608Metric
R5, R6: 10k; R_0603_1608Metric
U1: VN-100
U2, U3: ISOW7842; SOIC-16W_7.5x10.3mm_P1.27mm
U4: MAX3221E; TSSOP-16_4.4x5mm_P0.65mm
U5, U6: SN74AXCH8T245; TSSOP-24_4.4x7.8mm_P0.65mm
U7: SN74AVCH2T45; VSSOP-8_2.3x2mm_P0.5mm
U8: FT230XS; SSOP-16_3.9x4.9mm_P0.635mm
U9: uIMU-2

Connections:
+1V2: J2.11, J2.13
+1V8: C14.1, C15.1, C18.1, J2.1, J2.2, U5.1, U5.2, U5.11, U6.1, U6.2, U6.11, U7.1, U7.5
+3V3: C1.1, C2.1, C5.1, C6.1, C16.1, C17.1, C19.1, FB2.1, J2.5, J2.7, J8.1, U1.10, U2.1, U3.1, U5.23, U5.24, U6.23, U6.24, U7.8
/BONUS_INPUT: J8.3, U6.16
/GPIO0_1V8: J2.4, U5.10
/GPIO1A: U2.3, U5.19
/GPIO1A_ISO: J1.1, U2.14
/GPIO1B: U2.4, U5.18
/GPIO1B_ISO: J1.2, U2.13
/GPIO1C: U2.5, U5.17
/GPIO1C_ISO: J1.3, R5.1, U2.12
/GPIO1D: U2.6, U5.16
/GPIO1D_ISO: J1.4, R6.1, U2.11
/GPIO1_1V8: J2.6, U5.9
/GPIO1_GND_ISO: C3.2, C4.2, J1.5, R5.2, R6.2, U2.9, U2.10, U2.15
/GPIO1_VCC_ISO: C3.1, C4.1, U2.16
/GPIO2_1V8: J2.8, U5.8
/GPIO3_1V8: J2.10, U5.7
/GPIO4_1V8: J2.12, U5.6
/GPIO5_1V8: J2.14, U5.5
/GPIO6_1V8: J2.16, U5.4
/GPIO7_1V8: J2.18, U5.3
/GPIO8_1V8: J2.21, U6.3
/GPIO9_1V8: J2.23, U6.4
/GPIO10_1V8: J2.25, U6.5
/GPIO11_1V8: J2.27, U6.6
/GPIO12_1V8: J2.26, U6.7
/GPIO13_1V8: J2.24, U6.8
/GPIO14_1V8: J2.22, U6.9
/GPIO15_1V8: J2.20, U6.10
/GPIO16_1V8: J2.17, U7.2
/GPIO17_1V8: J2.19, U7.3
/IMU_CS: J9.2, U1.23, U7.6, U9.8
/IMU_MISO: J8.4, U1.19, U6.15, U9.7
/IMU_MOSI: J8.7, U1.17, U6.20, U9.6
/IMU_NRST: J8.10, U1.21, U6.21, U9.12
/IMU_RX0: J7.2, U9.18
/IMU_RX1: J8.5, U1.13, U6.18
/IMU_RX2: J6.2, U1.6
/IMU_SCK: J8.8, U1.16, U6.19, U9.9
/IMU_SYNC_IN: J9.1, U1.22, U7.7, U9.5
/IMU_SYNC_OUT: J8.2, U1.9, U6.14, U9.20
/IMU_TX0: J7.1, U9.19
/IMU_TX1: J8.6, U1.12, U6.17
/IMU_TX2: J6.1, U1.5
/ISO_GND_RS232: C7.2, C8.2, C11.2, C12.1, C13.1, J4.3, U3.9, U3.10, U3.15, U4.1, U4.14
/ISO_RS232_DIN: U3.14, U4.11
/ISO_RS232_DOUT: J4.1, U4.13
/ISO_RS232_FORCEON: U3.13, U4.12
/ISO_RS232_INVALID: U3.11, U4.10
/ISO_RS232_RIN: J4.2, U4.8
/ISO_RS232_ROUT: U3.12, U4.9
/ISO_VCC_RS232: C7.1, C8.1, C11.1, U3.16, U4.15, U4.16
/ROOT_RX: J2.28, J3.1, U8.1
/ROOT_TX: J2.30, J3.2, U8.4
/RS232_DIN: U3.3, U5.21
/RS232_FORCEON: U3.4, U5.20
/RS232_INVALID: U3.6, U5.14
/RS232_ROUT: U3.5, U5.15
/RXLED: R3.2, U8.14
/TXLED: R4.2, U8.7
/USB_3V3: C25.1, D1.2, D2.2, U8.3, U8.10, U8.11
/USB_DM: R2.1, U8.9
/USB_DP: R1.1, U8.8
/USB_VCC: C23.1, C24.1, FB1.1, U8.12
GND: C1.2, C2.2, C5.2, C6.2, C14.2, C15.2, C16.2, C17.2, C18.2, C19.2, C20.2, C21.2, C22.2, C23.2, C24.2, C25.2, C26.2, J2.3, J2.9, J2.15, J2.29, J3.3, J5.5, J6.3, J7.3, J8.9, J9.3, U1.1, U1.2, U1.3, U1.4, U1.18, U1.28, U1.30, U2.2, U2.8, U3.2, U3.8, U5.12, U5.13, U5.22, U6.12, U6.13, U6.22, U7.4, U8.5, U8.13, U9.10, U9.11, U9.21
unnamed: C9.1, U4.2
unnamed: C9.2, U4.4
unnamed: C10.1, U4.5
unnamed: C10.2, U4.6
unnamed: C12.2, U4.3
unnamed: C13.2, U4.7
unnamed: C20.1, J5.3, R1.2
unnamed: C21.1, FB1.2, J5.1
unnamed: C22.1, J5.2, R2.2
unnamed: C26.1, FB2.2, U9.3, U9.22
unnamed: D1.1, R3.1
unnamed: D2.1, R4.1
